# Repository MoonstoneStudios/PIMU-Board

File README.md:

# PIMU Suite

- MicroSD Card symbol, footprint, and model credit to SnapEDA
- Teensy symbols and footprint credit to https://github.com/XenGi/teensy_library
- IMU and pressure footprints credit to Adafruit (I made the symbol, not the footprints)

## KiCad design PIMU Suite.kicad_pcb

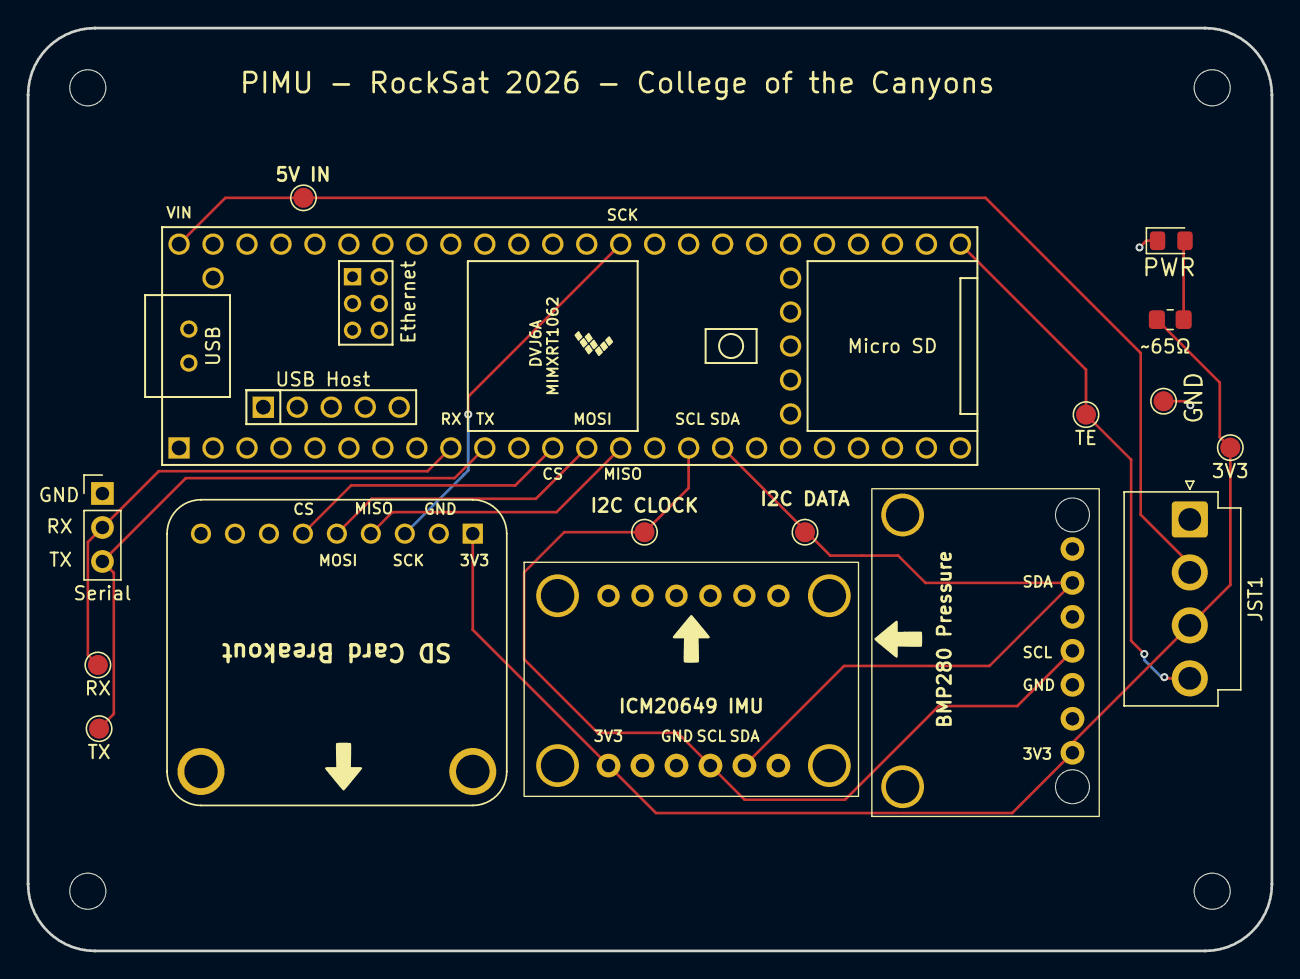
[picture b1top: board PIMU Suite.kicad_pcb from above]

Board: 2 copper layers, 93.0 x 69.0 mm, 16 parts (0 on the bottom side), 13 nets.

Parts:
BMP1: BMP280
D1: LED; LED_0805_2012Metric_Pad1.15x1.40mm_HandSolder
HEADER1: Serial; PinHeader_1x03_P2.54mm_Vertical
IMU1: ICM20649; IMU
JST1: JST_VH_B4P-VH-B; JST_VH_B4P-VH-B_1x04_P3.96mm_Vertical
R1: ~65Ω; R_0805_2012Metric_Pad1.20x1.40mm_HandSolder
TEENSY1: Teensy4.1; Teensy41
TP1: 5V IN; TestPoint_Pad_D1.5mm
TP2: GND CONN; TestPoint_Pad_D1.5mm
TP3: I2C CLOCK; TestPoint_Pad_D1.5mm
TP4: I2C DATA; TestPoint_Pad_D1.5mm
TP5: 3V3; TestPoint_Pad_D1.5mm
TP6: TE; TestPoint_Pad_D1.5mm
TP7: TX; TestPoint_Pad_D1.5mm
TP8: RX; TestPoint_Pad_D1.5mm
U2: MICROSD_SPI_OR_SDIO_CARD; MODULE_MICROSD_SPI_OR_SDIO_CARD

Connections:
+3.3V: BMP1.1 (VIN), IMU1.7 (VIN), JST1.3, R1.2, TP5.1, U2.1 (3V)
+5V: JST1.2, TEENSY1.48 (VIN), TP1.1
/SCL_LINE: BMP1.4 (SCK), IMU1.10 (SCL), TEENSY1.16 (24_A10_TX6_SCL2), TP3.1
/SDA_LINE: BMP1.6 (SDI), IMU1.11 (SDA), TEENSY1.17 (25_A11_RX6_SDA2), TP4.1
/SD_CS: TEENSY1.12 (10_CS_MQSR), U2.6 (D3/CS)
/SD_MISO: TEENSY1.14 (12_MISO_MQSL), U2.4 (D0/SO)
/SD_MOSI: TEENSY1.13 (11_MOSI_CTX1), U2.5 (CMD/SI)
/SD_SCK: TEENSY1.35 (13_SCK_LED), U2.3 (CLK)
/TE: JST1.4, TEENSY1.25 (33_MCLK2), TP6.1
/UART_FROM_TEENSY: HEADER1.3, TEENSY1.10 (8_TX2_IN1), TP7.1
/UART_TO_TEENSY: HEADER1.2, TEENSY1.9 (7_RX2_OUT1A), TP8.1
GND: BMP1.3 (GND), D1.1 (K), HEADER1.1, IMU1.9 (GND), JST1.1, TEENSY1.1 (GND), TP2.1, U2.2 (GND)
unnamed: D1.2 (A), R1.1

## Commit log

2025-10-27 initial
    traces are done by an algorithm and is 2 sided
2025-11-02 hand-routed
2025-11-03 added pressure
2025-11-03 Using new pressure sensor
2025-11-03 Actually use correct sensor
2025-11-07 Removed ignored backups
2025-11-07 Made I2C lines same length
2025-11-11 Cleanup
2025-11-16 Added impl note
2025-11-17 Change pwer dist.
2025-11-17 Fix mistake from prev
    also added a wire for the detect pin
2025-11-22 Nicer routes
2025-11-26 New JST
    also added THT resistor and LED, but the footprint will change soon
2025-12-17 change footprints
2025-12-17 update copper fill size
2025-12-17 Haldsolder footprints
2026-01-03 Updates from team
2026-01-03 Fix JST order
2026-01-03 Tweaked for manufactering
2026-01-03 Update silk
2026-01-04 Add TE line
2026-01-06 Rename value
2026-01-06 PCBWay Limitations
2026-01-06 Final updates
2026-01-07 PCB export
2026-01-10 Fix wrong wiring
2026-02-04 JLCPCB specs
2026-02-04 Fillits and bore holes:
2026-02-07 Move JST
2026-02-12 tx rx
2026-02-14 USB headers + silkscreen
